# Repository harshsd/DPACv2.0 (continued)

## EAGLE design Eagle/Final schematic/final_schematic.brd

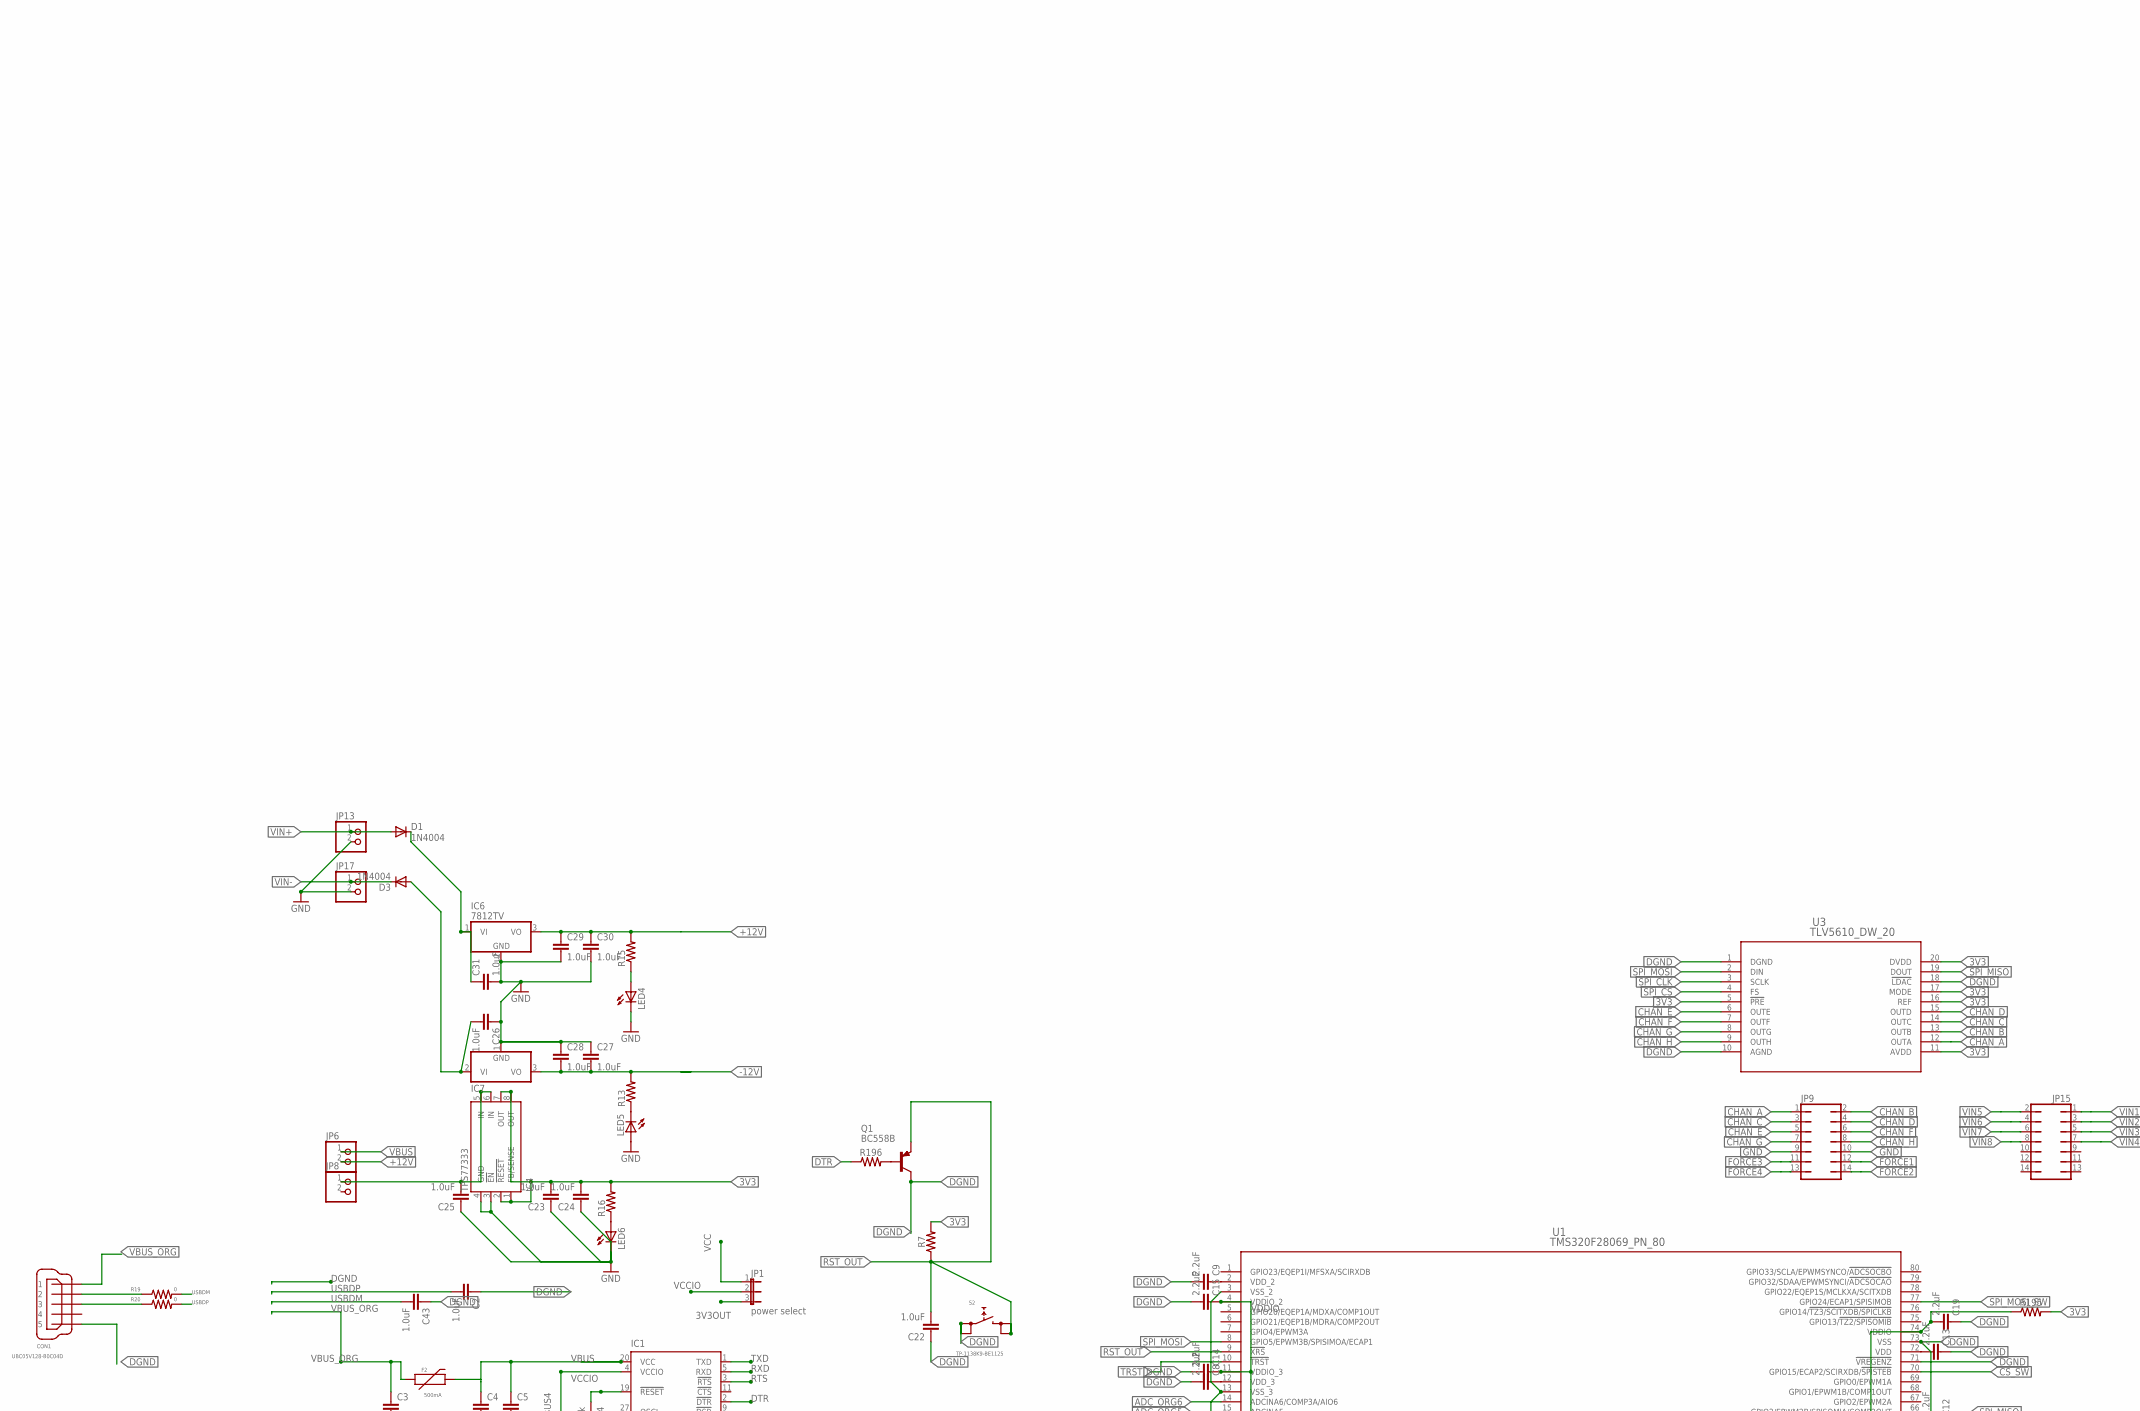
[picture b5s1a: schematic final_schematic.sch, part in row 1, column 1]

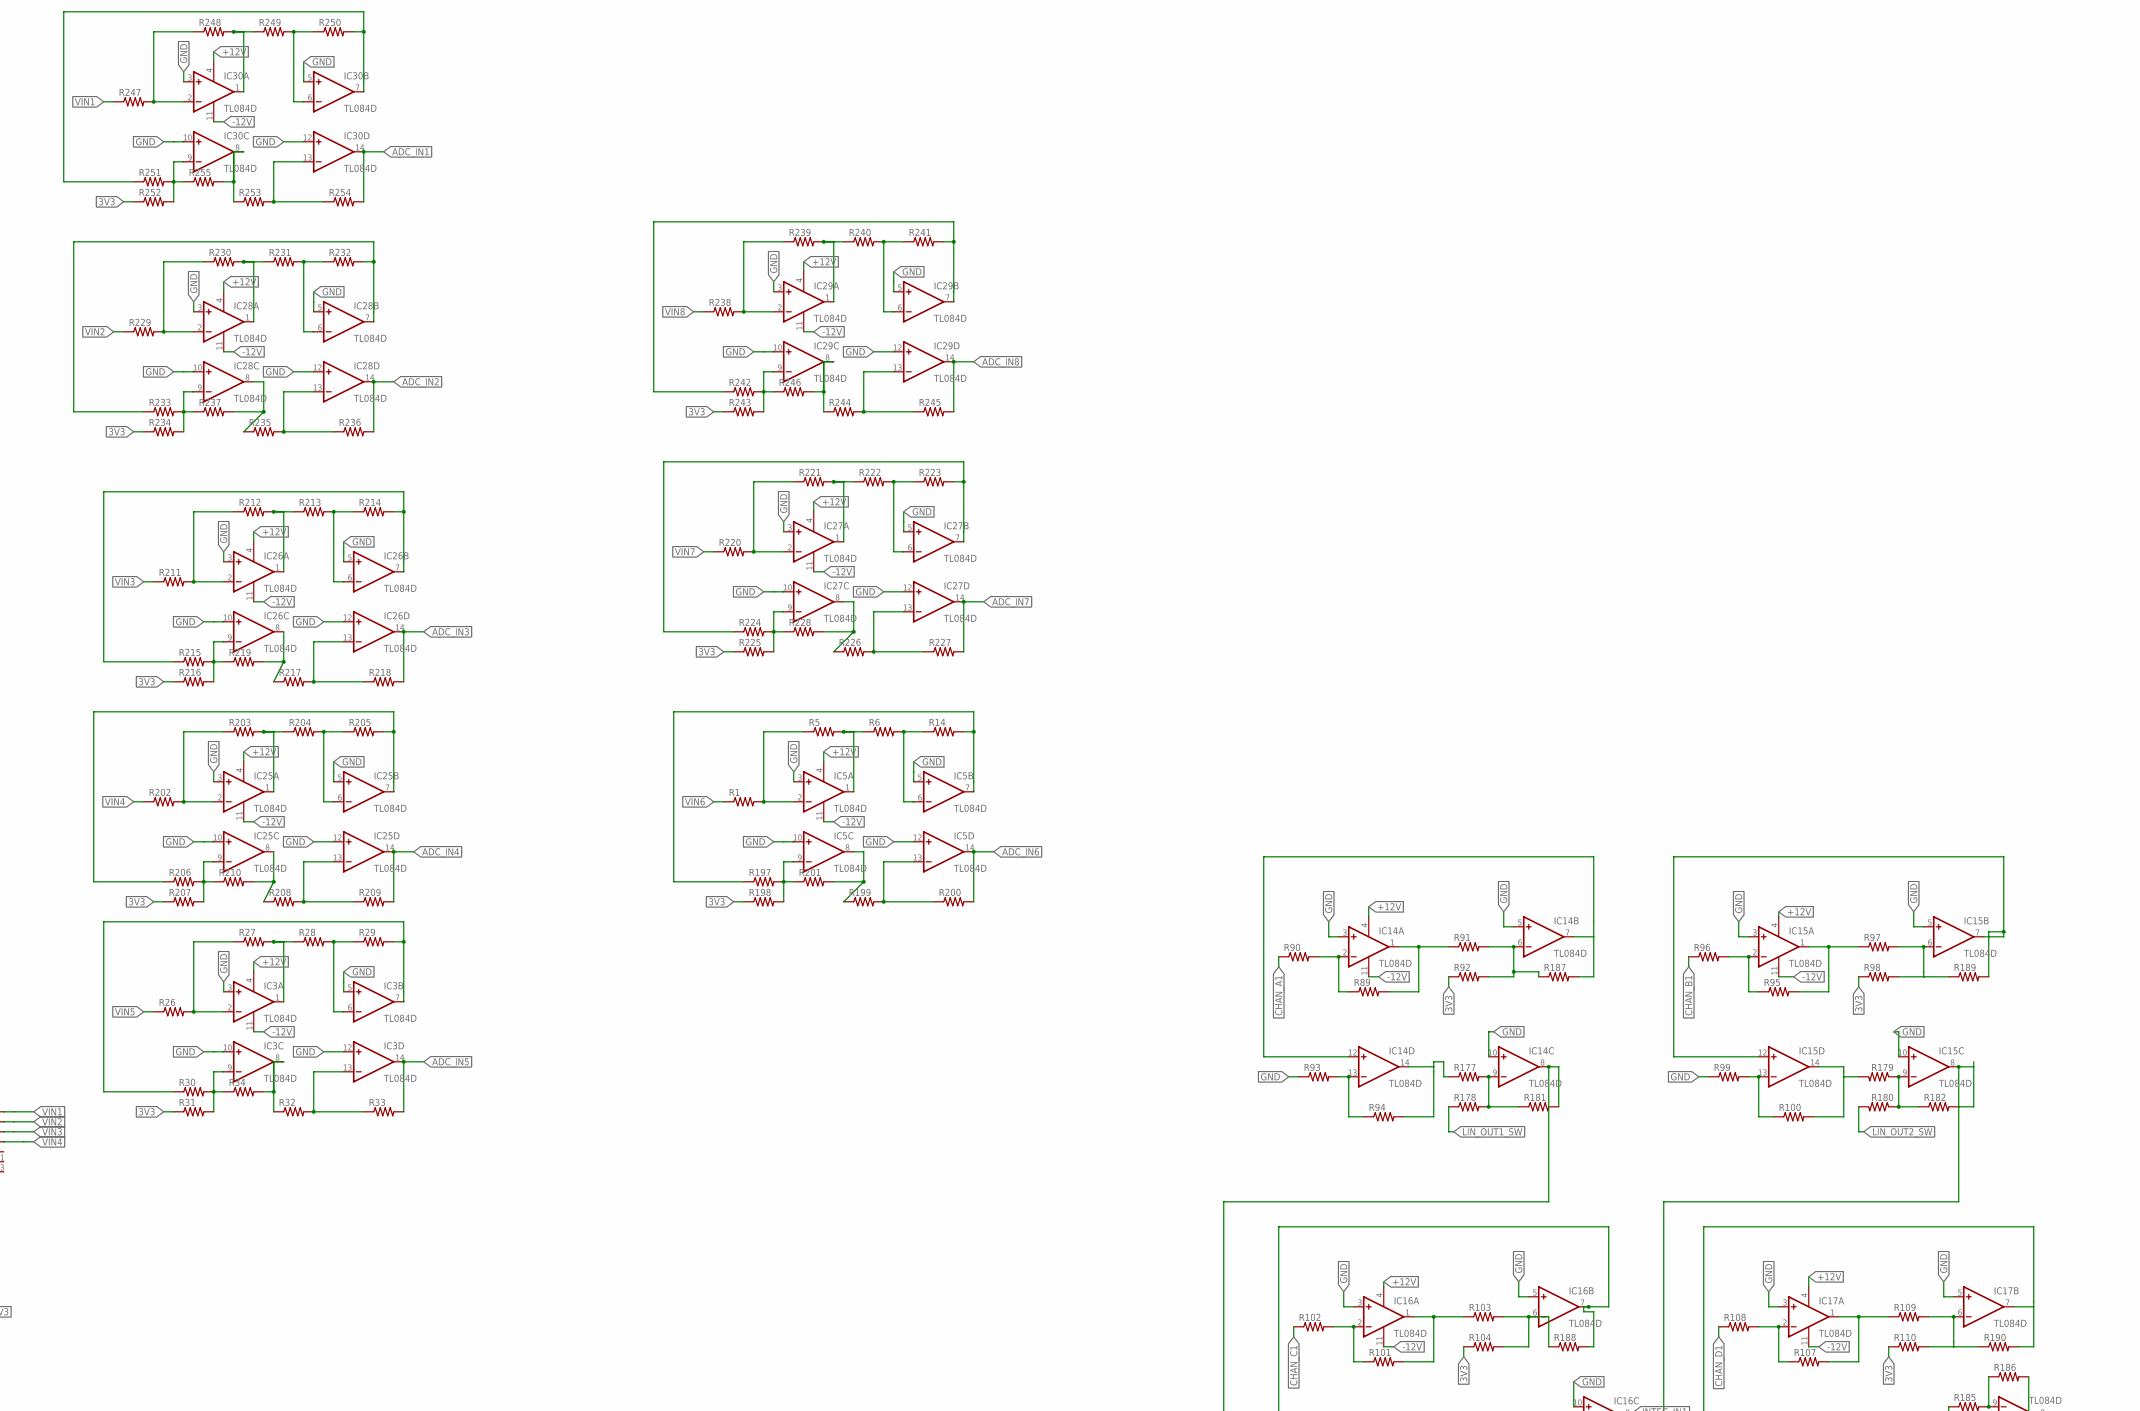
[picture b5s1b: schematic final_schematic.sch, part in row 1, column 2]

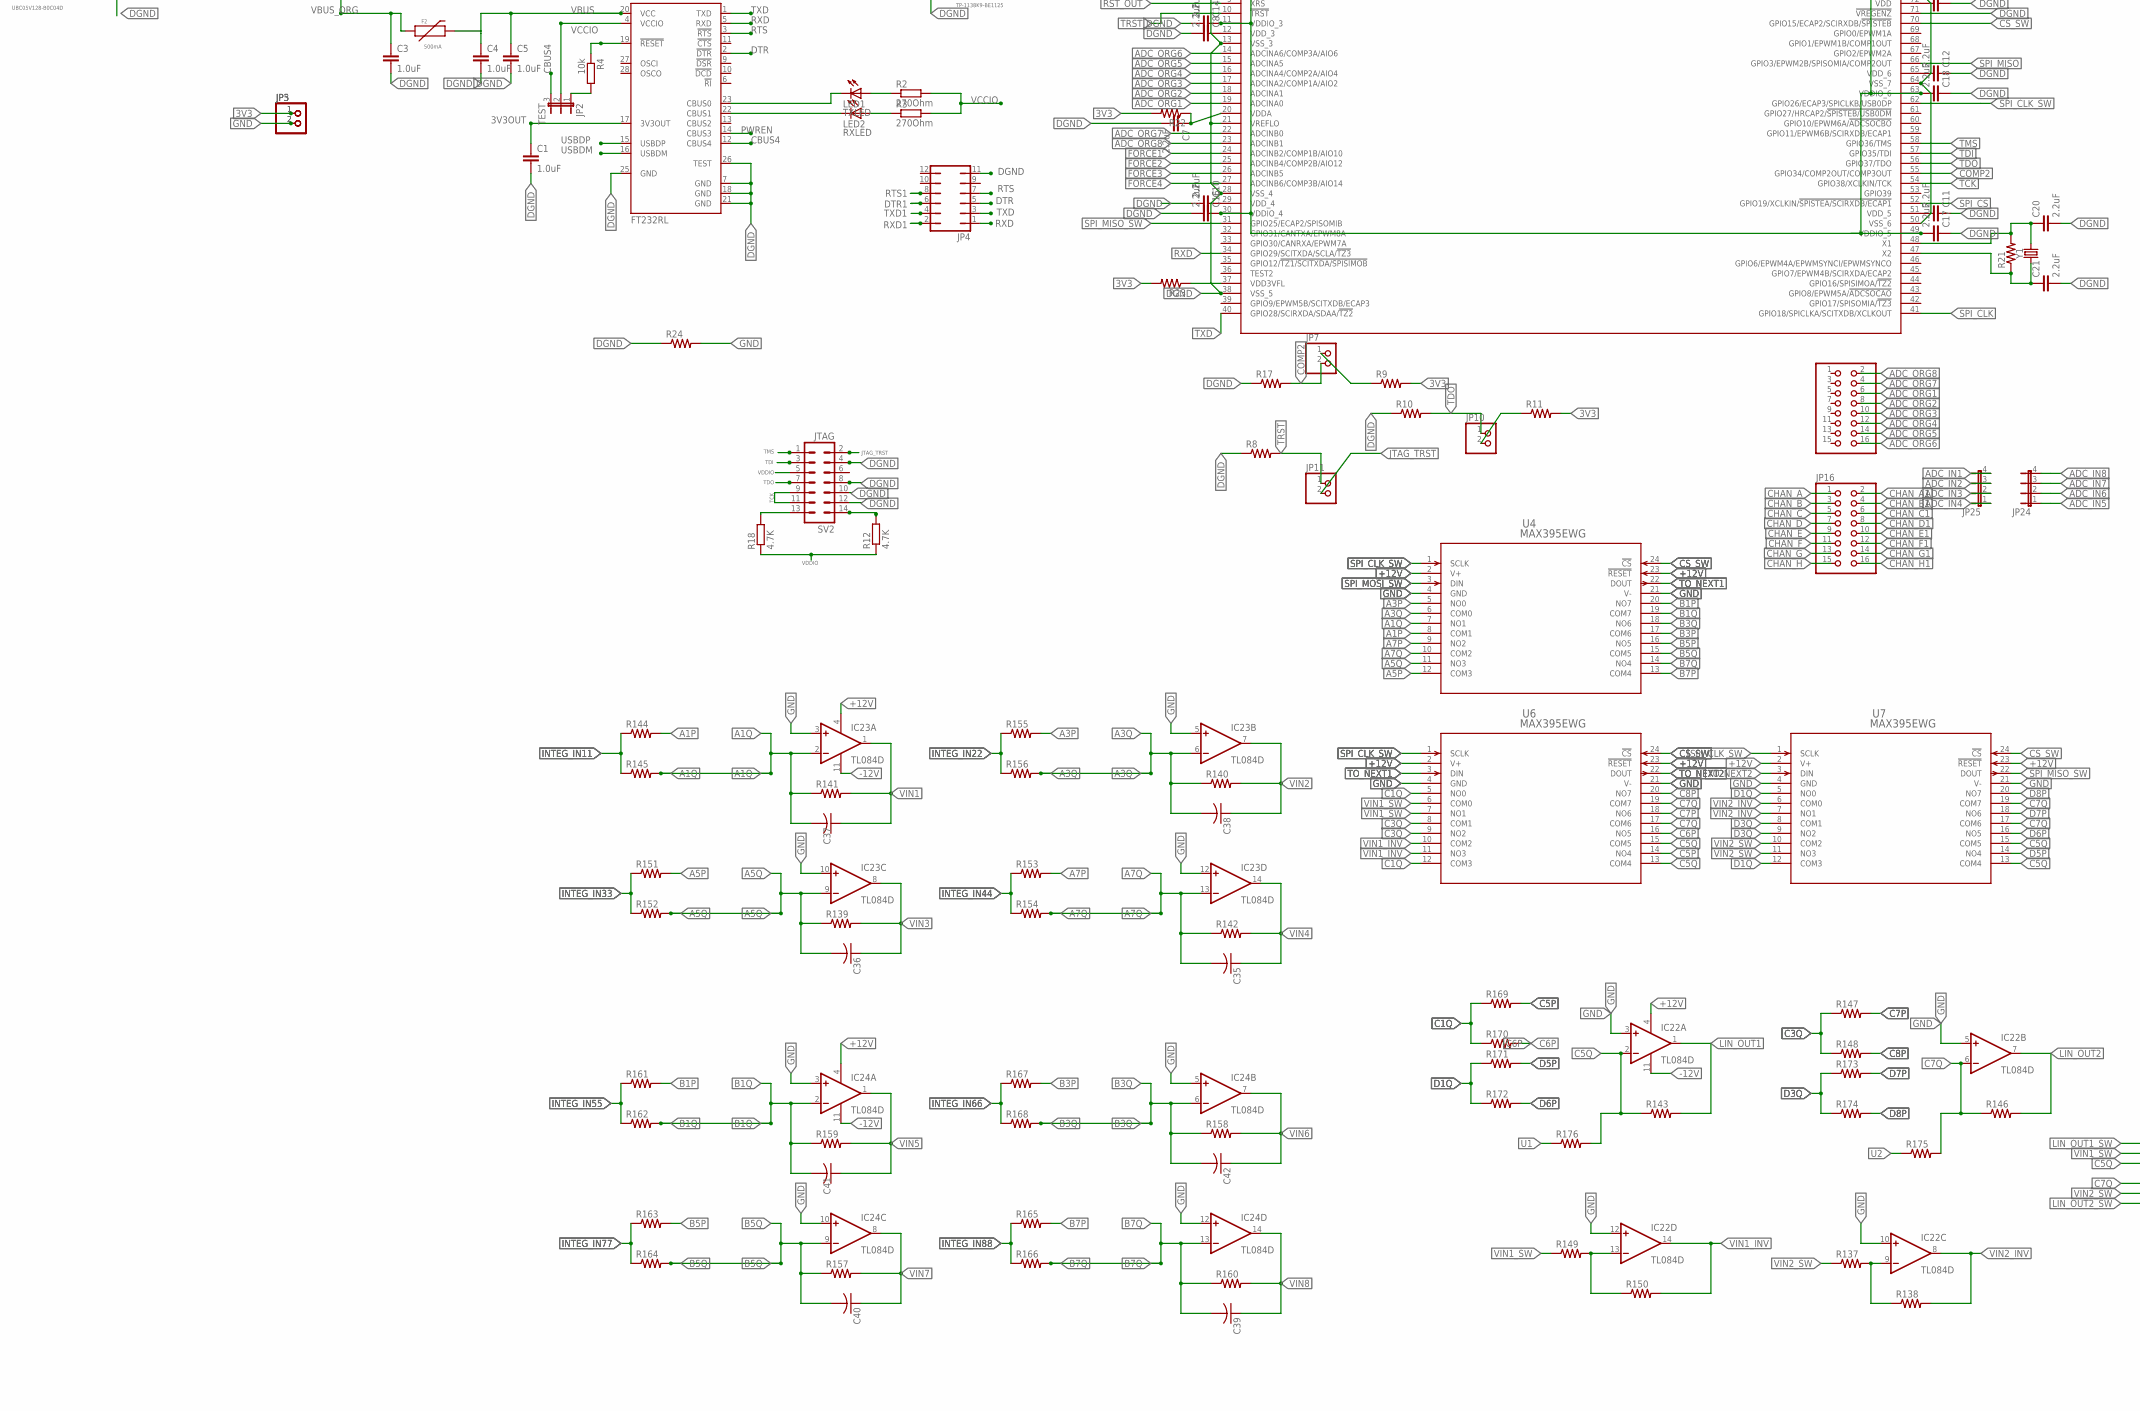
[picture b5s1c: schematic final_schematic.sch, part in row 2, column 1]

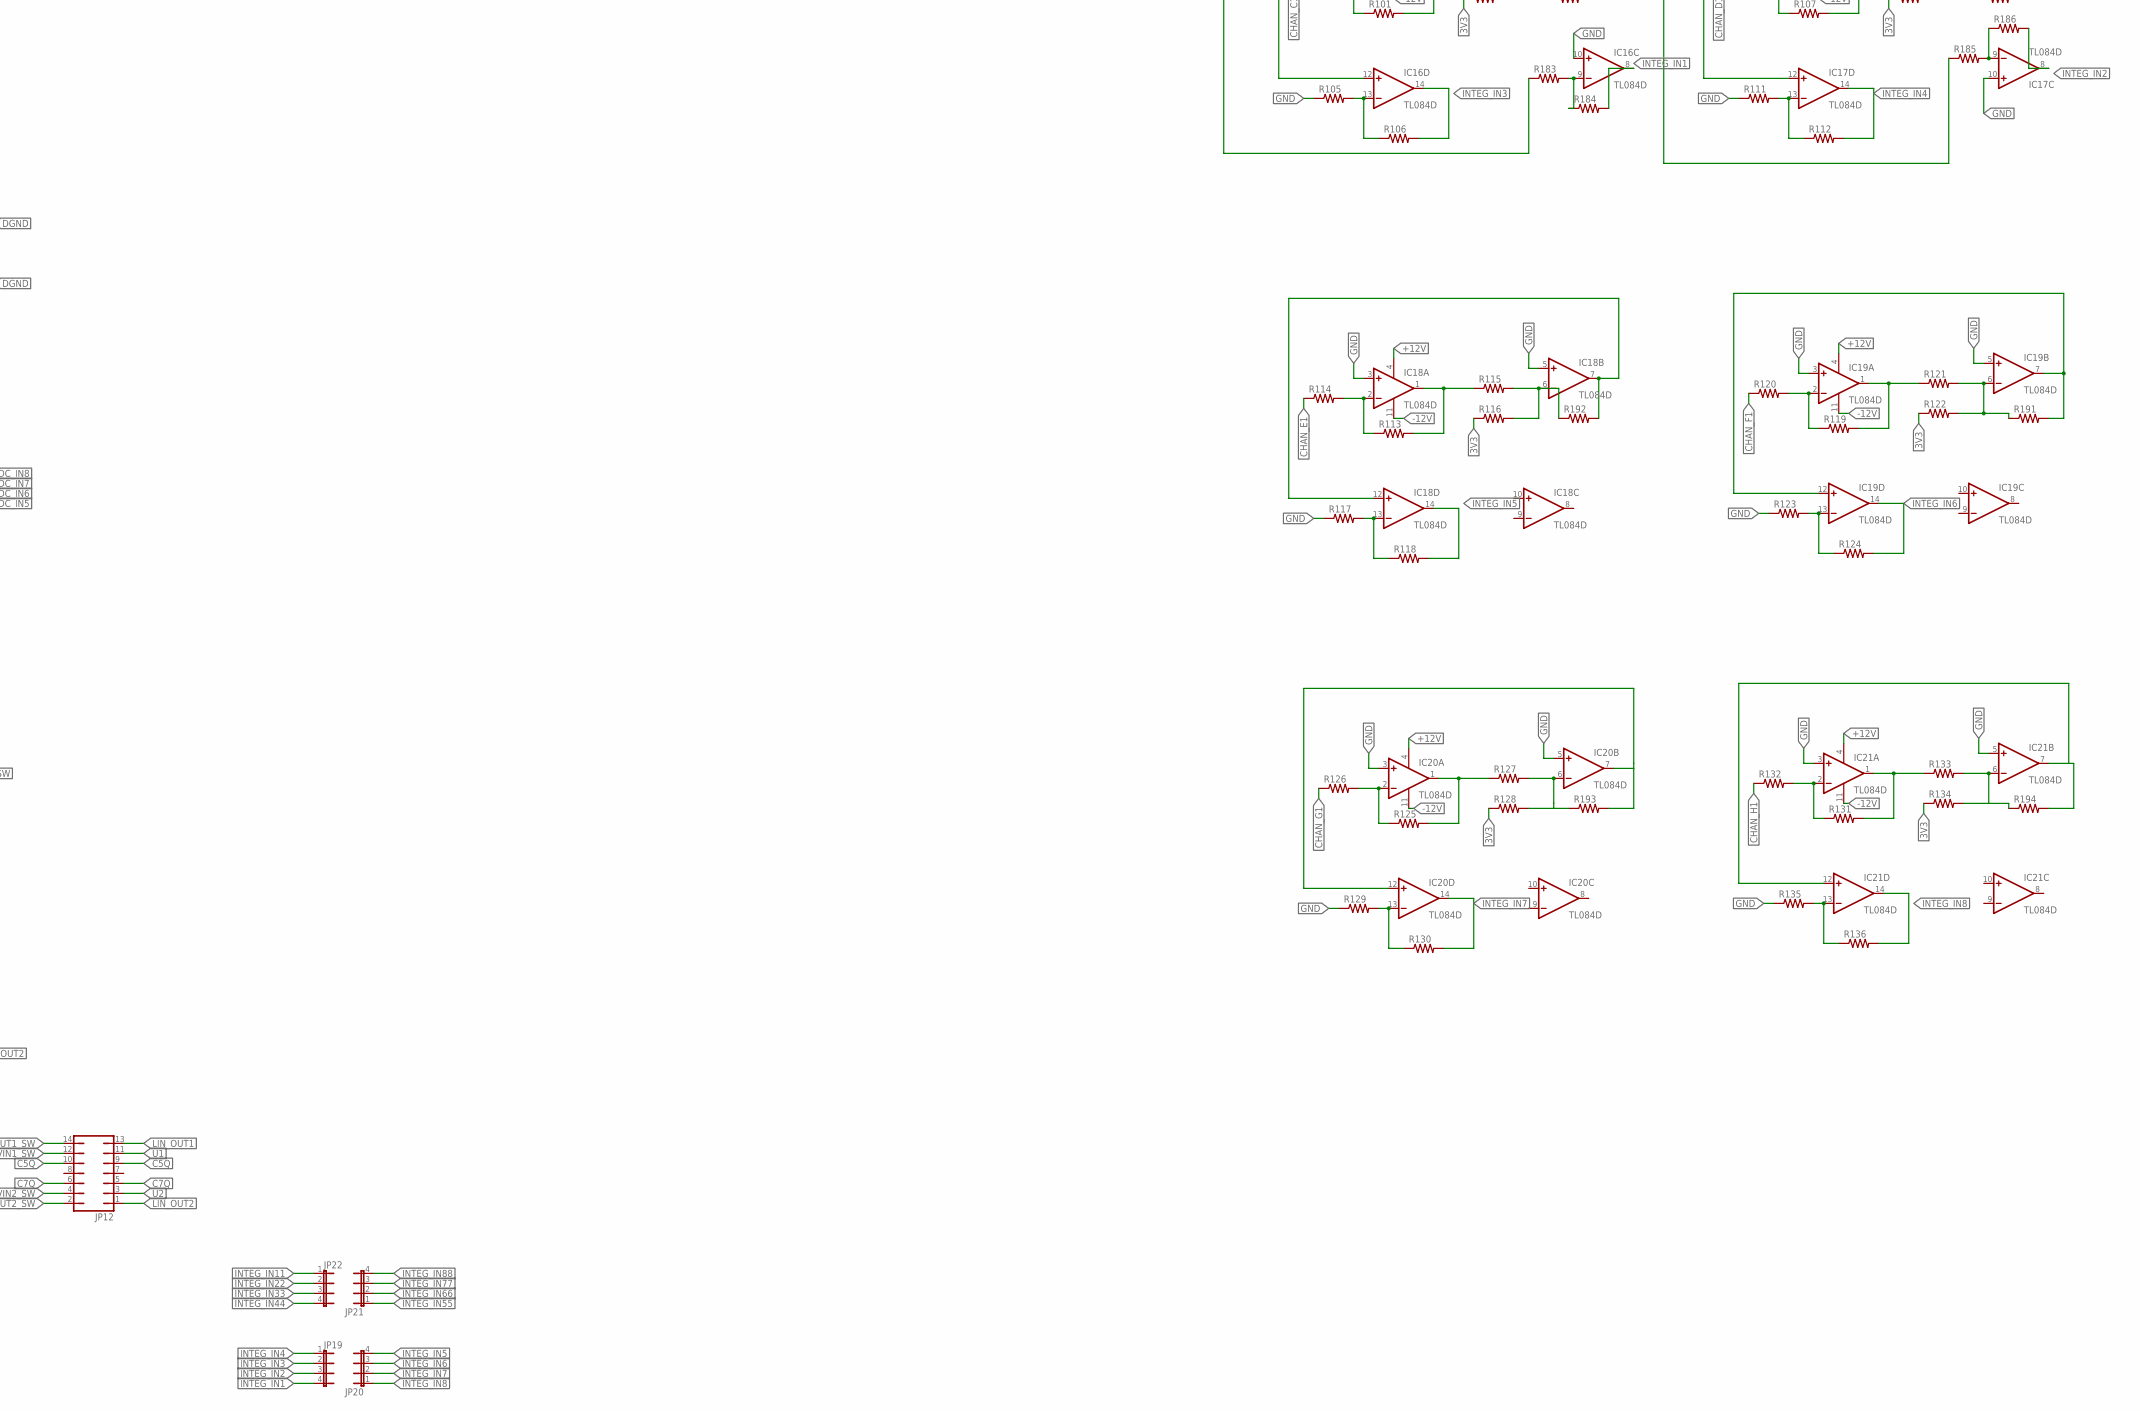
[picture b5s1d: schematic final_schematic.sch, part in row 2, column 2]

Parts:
C1, C2, C3, C4, C5, C22, C23, C24, C25, C26, C27, C28, C29, C30, C31, C43: 1.0uF; 1206
C7, C8, C9, C10, C11, C12, C13, C14, C15, C16, C17, C18, C19, C20, C21: 2.2uF; 1206
C35, C36, C37, C38, C39, C40, C41, C42: C-USC1206; C1206
CON1: UBC05V128-B0C04D; 32005-201
D1, D3: 1N4004; DO41-10
F2: 500mA; PTC-1206
IC1: FT232RL; SSOP28
IC3, IC5, IC14, IC15, IC16, IC17, IC18, IC19, IC20, IC21, IC22, IC23, IC24, IC25, IC26, IC27, IC28, IC29, IC30: TL084D; SO14
IC4: TPS77333; DGK_S-PDSO-G8
IC6: 7812TV; TO220V
IC7: 7912T; TO220H
JP1: power select; JP2
JP2: TEST; JP2
JP3, JP5, JP6, JP7, JP8, JP10, JP11, JP13, JP17: PINHD-1X2; 1X02
JP4: JP6Q
JP9, JP12, JP15: JP7Q
JP16, JP18: PINHD-2X8; 2X08
JP19, JP20, JP21, JP22, JP24, JP25: JP4E; JP4
LED1: TXLED; CHIPLED_1206
LED2: RXLED; CHIPLED_1206
LED4, LED5, LED6: LED3MM
Q1: BC558B; TO92-EBC
R1, R5, R6, R8, R9, R10, R11, R13, R14, R15, R16, R17, R21, R22, R23, R26, R27, R28, R29, R30, R31, R32, R33, R34, R89, R90, R91, R92, R93, R94, R95, R96, R97, R98, R99, R100, R101, R102, R103, R104, R105, R106, R107, R108, R109, R110, R111, R112, R113, R114, R115, R116, R117, R118, R119, R120, R121, R122, R123, R124, R125, R126, R127, R128, R129, R130, R131, R132, R133, R134, R135, R136, R137, R138, R139, R140, R141, R142, R143, R144, R145, R146, R147, R148, R149, R150, R151, R152, R153, R154, R155, R156, R157, R158, R159, R160, R161, R162, R163, R164, R165, R166, R167, R168, R169, R170, R171, R172, R173, R174, R175, R176, R177, R178, R179, R180, R181, R182, R183, R184, R185, R186, R187, R188, R189, R190, R191, R192, R193, R194, R197, R198, R199, R200, R201, R202, R203, R204, R205, R206, R207, R208, R209, R210, R211, R212, R213, R214, R215, R216, R217, R218, R219, R220, R221, R222, R223, R224, R225, R226, R227, R228, R229, R230, R231, R232, R233, R234, R235, R236, R237, R238, R239, R240, R241, R242, R243, R244, R245, R246, R247, R248, R249, R250, R251, R252, R253, R254, R255: R-US_R1206; R1206
R2, R3: 270Ohm; M1206
R4: 10k; M1206
R7, R195, R196: 1206
R12, R18: 4.7K; M1206
R19: 0; R1206
R20: 0; R1206W
R24: R-US_0207/7; 0207/7
S2: TP-1138K9-BE1125; FSMJSMA
SV2: JTAG; MA07-2
U1: TMS320F28069_PN_80; PN80
U3: TLV5610_DW_20; DW20
U4, U6, U7: MAX395EWG; 21-0042B_24
Y1: CRYSTALPTH-HC49UV; HC49U

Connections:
3V3: C23.2, C24.2, IC4.1 (FB/SENSE), IC4.2 (!RESET), IC4.7 (OUT), IC4.8 (OUT), JP3.1, JP5.1, R7.2, R9.2, R11.2, R16.2, R22.2, R23.2, R31.1, R92.1, R98.1, R104.1, R110.1, R116.1, R122.1, R128.1, R134.1, R195.2, R198.1, R207.1, R216.1, R225.1, R234.1, R243.1, R252.1, U3.5 (!PRE), U3.11 (AVDD), U3.16 (REF), U3.17 (MODE), U3.20 (DVDD)
3V3OUT: C1.1, IC1.17 (3V3OUT), JP1.3
+12V: C29.1, C30.1, IC3.4 (V+), IC5.4 (V+), IC6.3 (VO), IC14.4 (V+), IC15.4 (V+), IC16.4 (V+), IC17.4 (V+), IC18.4 (V+), IC19.4 (V+), IC20.4 (V+), IC21.4 (V+), IC22.4 (V+), IC23.4 (V+), IC24.4 (V+), IC25.4 (V+), IC26.4 (V+), IC27.4 (V+), IC28.4 (V+), IC29.4 (V+), IC30.4 (V+), JP6.2, R15.2, U4.2 (V+), U4.23 (!RESET), U6.2 (V+), U6.23 (!RESET), U7.2 (V+), U7.23 (!RESET)
-12V: C27.2, C28.2, IC3.11 (V-), IC5.11 (V-), IC7.3 (VO), IC14.11 (V-), IC15.11 (V-), IC16.11 (V-), IC17.11 (V-), IC18.11 (V-), IC19.11 (V-), IC20.11 (V-), IC21.11 (V-), IC22.11 (V-), IC23.11 (V-), IC24.11 (V-), IC25.11 (V-), IC26.11 (V-), IC27.11 (V-), IC28.11 (V-), IC29.11 (V-), IC30.11 (V-), R13.2
A1P: R144.2, U4.8 (COM1)
A1Q: C37.2, IC23.2 (-IN), R141.1, R145.2, U4.7 (NO1)
A3P: R155.2, U4.5 (NO0)
A3Q: C38.2, IC23.6 (-IN), R140.1, R156.2, U4.6 (COM0)
A5P: R151.2, U4.12 (COM3)
A5Q: C36.2, IC23.9 (-IN), R139.1, R152.2, U4.11 (NO3)
A7P: R153.2, U4.9 (NO2)
A7Q: C35.2, IC23.13 (-IN), R142.1, R154.2, U4.10 (COM2)
ADC_IN1: IC30.14 (OUT), JP25.4, R254.2
ADC_IN2: IC28.14 (OUT), JP25.3, R236.2
ADC_IN3: IC26.14 (OUT), JP25.2, R218.2
ADC_IN4: IC25.14 (OUT), JP25.1, R209.2
ADC_IN5: IC3.14 (OUT), JP24.1, R33.2
ADC_IN6: IC5.14 (OUT), JP24.2, R200.2
ADC_IN7: IC27.14 (OUT), JP24.3, R227.2
ADC_IN8: IC29.14 (OUT), JP24.4, R245.2
ADC_ORG1: JP18.6, U1.19 (ADCINA0)
ADC_ORG2: JP18.8, U1.18 (ADCINA1)
ADC_ORG3: JP18.10, U1.17 (ADCINA2/COMP1A/AIO2)
ADC_ORG4: JP18.12, U1.16 (ADCINA4/COMP2A/AIO4)
ADC_ORG5: JP18.14, U1.15 (ADCINA5)
ADC_ORG6: JP18.16, U1.14 (ADCINA6/COMP3A/AIO6)
ADC_ORG7: JP18.4, U1.22 (ADCINB0)
ADC_ORG8: JP18.2, U1.23 (ADCINB1)
B1P: R161.2, U4.20 (NO7)
B1Q: C41.2, IC24.2 (-IN), R159.1, R162.2, U4.19 (COM7)
B3P: R167.2, U4.17 (COM6)
B3Q: C42.2, IC24.6 (-IN), R158.1, R168.2, U4.18 (NO6)
B5P: R163.2, U4.16 (NO5)
B5Q: C40.2, IC24.9 (-IN), R157.1, R164.2, U4.15 (COM5)
B7P: R165.2, U4.13 (COM4)
B7Q: C39.2, IC24.13 (-IN), R160.1, R166.2, U4.14 (NO4)
C1Q: R169.1, R170.1, U6.5 (NO0), U6.12 (COM3)
C3Q: R147.1, R148.1, U6.8 (COM1), U6.9 (NO2)
C5P: R169.2, U6.14 (NO4)
C5Q: IC22.2 (-IN), JP12.9, JP12.10, R143.1, R176.2, U6.13 (COM4), U6.15 (COM5), U7.13 (COM4), U7.15 (COM5)
C6P: R170.2, U6.16 (NO5)
C7P: R147.2, U6.18 (NO6)
C7Q: IC22.6 (-IN), JP12.5, JP12.6, R146.1, R175.2, U6.17 (COM6), U6.19 (COM7), U7.17 (COM6), U7.19 (COM7)
C8P: R148.2, U6.20 (NO7)
CBUS4: IC1.12 (CBUS4), JP2.3
CHAN_A: JP9.1, JP16.1, U3.12 (OUTA)
CHAN_A1: JP16.2, R90.1
CHAN_B: JP9.2, JP16.3, U3.13 (OUTB)
CHAN_B1: JP16.4, R96.1
CHAN_C: JP9.3, JP16.5, U3.14 (OUTC)
CHAN_C1: JP16.6, R102.1
CHAN_D: JP9.4, JP16.7, U3.15 (OUTD)
CHAN_D1: JP16.8, R108.1
CHAN_E: JP9.5, JP16.9, U3.6 (OUTE)
CHAN_E1: JP16.10, R114.1
CHAN_F: JP9.6, JP16.11, U3.7 (OUTF)
CHAN_F1: JP16.12, R120.1
CHAN_G: JP9.7, JP16.13, U3.8 (OUTG)
CHAN_G1: JP16.14, R126.1
CHAN_H: JP9.8, JP16.15, U3.9 (OUTH)
CHAN_H1: JP16.16, R132.1
COMP2: JP7.2, R17.2, U1.55 (GPIO34/COMP2OUT/COMP3OUT)
CS_SW: U1.70 (GPIO15/ECAP2/SCIRXDB/!SPISTEB), U4.24 (!CS), U6.24 (!CS), U7.24 (!CS)
D1Q: R171.1, R172.1, U7.5 (NO0), U7.12 (COM3)
D3Q: R173.1, R174.1, U7.8 (COM1), U7.9 (NO2)
D5P: R171.2, U7.14 (NO4)
D6P: R172.2, U7.16 (NO5)
D7P: R173.2, U7.18 (NO6)
D8P: R174.2, U7.20 (NO7)
DGND: C1.2, C2.1, C3.2, C4.2, C5.2, C7.2, C8.2, C9.2, C10.2, C11.1, C12.1, C13.1, C14.2, C15.2, C16.2, C17.1, C18.1, C19.1, C20.2, C21.2, C22.1, C43.1, CON1.5, IC1.7 (GND), IC1.18 (GND), IC1.21 (GND), IC1.25 (GND), IC1.26 (TEST), JP4.11, Q1.C, R8.1, R10.1, R17.1, R24.1, S2.P$1 (0), S2.P$2 (0), SV2.4, SV2.8, SV2.10, SV2.12, U1.3 (VSS_2), U1.13 (VSS_3), U1.21 (VREFLO), U1.28 (VSS_4), U1.38 (VSS_5), U1.50 (VSS_6), U1.64 (VSS_7), U1.71 (!VREGENZ), U1.73 (VSS), U3.1 (DGND), U3.10 (AGND), U3.18 (!LDAC)
DTR: IC1.2 (!DTR), JP4.5, R196.1
DTR1: JP4.6
FORCE1: JP9.12, U1.24 (ADCINB2/COMP1B/AIO10)
FORCE2: JP9.14, U1.25 (ADCINB4/COMP2B/AIO12)
FORCE3: JP9.11, U1.26 (ADCINB5)
FORCE4: JP9.13, U1.27 (ADCINB6/COMP3B/AIO14)
GND: C23.1, C24.1, C25.1, C26.1, C27.1, C28.1, C29.2, C30.2, C31.2, IC3.3 (+IN), IC3.5 (+IN), IC3.10 (+IN), IC3.12 (+IN), IC4.3 (!EN), IC4.4 (GND), IC5.3 (+IN), IC5.5 (+IN), IC5.10 (+IN), IC5.12 (+IN), IC6.2 (GND), IC7.1 (GND), IC14.3 (+IN), IC14.5 (+IN), IC14.10 (+IN), IC15.3 (+IN), IC15.5 (+IN), IC15.10 (+IN), IC16.3 (+IN), IC16.5 (+IN), IC16.10 (+IN), IC17.3 (+IN), IC17.5 (+IN), IC17.10 (+IN), IC18.3 (+IN), IC18.5 (+IN), IC19.3 (+IN), IC19.5 (+IN), IC20.3 (+IN), IC20.5 (+IN), IC21.3 (+IN), IC21.5 (+IN), IC22.3 (+IN), IC22.5 (+IN), IC22.10 (+IN), IC22.12 (+IN), IC23.3 (+IN), IC23.5 (+IN), IC23.10 (+IN), IC23.12 (+IN), IC24.3 (+IN), IC24.5 (+IN), IC24.10 (+IN), IC24.12 (+IN), IC25.3 (+IN), IC25.5 (+IN), IC25.10 (+IN), IC25.12 (+IN), IC26.3 (+IN), IC26.5 (+IN), IC26.10 (+IN), IC26.12 (+IN), IC27.3 (+IN), IC27.5 (+IN), IC27.10 (+IN), IC27.12 (+IN), IC28.3 (+IN), IC28.5 (+IN), IC28.10 (+IN), IC28.12 (+IN), IC29.3 (+IN), IC29.5 (+IN), IC29.10 (+IN), IC29.12 (+IN), IC30.3 (+IN), IC30.5 (+IN), IC30.10 (+IN), IC30.12 (+IN), JP3.2, JP5.2, JP9.9, JP9.10, JP13.2, JP17.2, LED4.K (C), LED5.A, LED6.K (C), R24.2, R93.1, R99.1, R105.1, R111.1, R117.1, R123.1, R129.1, R135.1, U4.4 (GND), U4.21 (V-), U6.4 (GND), U6.21 (V-), U7.4 (GND), U7.21 (V-)
INTEG_IN1: IC16.8 (OUT), JP19.4, R184.2
INTEG_IN2: IC17.8 (OUT), JP19.3, R186.2
INTEG_IN3: IC16.14 (OUT), JP19.2, R106.2
INTEG_IN4: IC17.14 (OUT), JP19.1, R112.2
INTEG_IN5: IC18.14 (OUT), JP20.4, R118.2
INTEG_IN6: IC19.14 (OUT), JP20.3, R124.2
INTEG_IN7: IC20.14 (OUT), JP20.2, R130.2
INTEG_IN8: IC21.14 (OUT), JP20.1, R136.2
INTEG_IN11: JP22.1, R144.1, R145.1
INTEG_IN22: JP22.2, R155.1, R156.1
INTEG_IN33: JP22.3, R151.1, R152.1
INTEG_IN44: JP22.4, R153.1, R154.1
INTEG_IN55: JP21.1, R161.1, R162.1
INTEG_IN66: JP21.2, R167.1, R168.1
INTEG_IN77: JP21.3, R163.1, R164.1
INTEG_IN88: JP21.4, R165.1, R166.1
JTAG_TRST: JP11.2, SV2.2
LIN_OUT1: IC22.1 (OUT), JP12.13, R143.2
LIN_OUT1_SW: JP12.14, R178.1
LIN_OUT2: IC22.7 (OUT), JP12.1, R146.2
LIN_OUT2_SW: JP12.2, R180.2
unnamed: C7.1, R22.1, U1.20 (VDDA)
unnamed: C8.1, U1.12 (VDD_3)
unnamed: C9.1, U1.2 (VDD_2)
unnamed: LED1.A, R2.1
unnamed: C10.1, U1.29 (VDD_4)
unnamed: C11.2, U1.51 (VDD_5)
unnamed: C12.2, U1.65 (VDD_6)
unnamed: C13.2, U1.72 (VDD)
unnamed: LED2.A, R3.1
unnamed: IC1.23 (CBUS0), LED1.C
unnamed: IC1.22 (CBUS1), LED2.C
unnamed: CON1.2, R19.1
unnamed: CON1.3, R20.1
unnamed: JP2.1, R4.2
unnamed: C20.1, R21.2, U1.48 (X1), Y1.2
unnamed: R23.1, U1.37 (VDD3VFL)
unnamed: C21.1, R21.1, U1.47 (X2), Y1.1
unnamed: JP7.1, R9.1
unnamed: Q1.B, R196.2
unnamed: JP10.2, R11.1
unnamed: R18.2, SV2.13
unnamed: C26.2, D3.A, IC7.2 (VI)
unnamed: R12.2, SV2.14
unnamed: C25.2, IC4.5 (IN), IC4.6 (IN), JP8.1
unnamed: LED4.A, R15.1
unnamed: C31.1, D1.C, IC6.1 (VI)
unnamed: IC14.2 (-IN), R89.1, R90.2
unnamed: LED5.K (C), R13.1
unnamed: LED6.A, R16.1
unnamed: IC3.2 (-IN), R26.2, R27.1
unnamed: IC3.1 (OUT), R27.2, R28.1
unnamed: IC3.6 (-IN), R28.2, R29.1
unnamed: IC5.2 (-IN), R1.2, R5.1
unnamed: IC3.8 (OUT), R32.1, R34.2
unnamed: IC14.1 (OUT), R89.2, R91.1
unnamed: IC3.13 (-IN), R32.2, R33.1
unnamed: IC3.9 (-IN), R30.2, R31.2, R34.1
unnamed: IC14.6 (-IN), R91.2, R92.2, R187.1
unnamed: IC14.13 (-IN), R93.2, R94.1
unnamed: IC14.8 (OUT), R181.2, R183.1
unnamed: IC14.7 (OUT), IC14.12 (+IN), R187.2
unnamed: IC15.2 (-IN), R95.1, R96.2
unnamed: IC15.1 (OUT), R95.2, R97.1
unnamed: IC15.6 (-IN), R97.2, R98.2, R189.1
unnamed: IC15.13 (-IN), R99.2, R100.1
unnamed: IC15.14 (OUT), R100.2, R179.2
unnamed: IC15.7 (OUT), IC15.12 (+IN), R189.2
unnamed: IC16.2 (-IN), R101.1, R102.2
unnamed: IC16.1 (OUT), R101.2, R103.1
unnamed: IC16.6 (-IN), R103.2, R104.2, R188.1
unnamed: IC16.13 (-IN), R105.2, R106.1
unnamed: IC14.9 (-IN), R177.2, R178.2, R181.1
unnamed: IC16.7 (OUT), IC16.12 (+IN), R188.2
unnamed: IC17.2 (-IN), R107.1, R108.2
unnamed: IC17.1 (OUT), R107.2, R109.1
unnamed: IC17.6 (-IN), R109.2, R110.2, R190.1
unnamed: IC17.13 (-IN), R111.2, R112.1
unnamed: IC15.9 (-IN), R179.1, R180.1, R182.1
unnamed: IC17.7 (OUT), IC17.12 (+IN), R190.2
unnamed: IC18.2 (-IN), R113.1, R114.2
unnamed: IC18.1 (OUT), R113.2, R115.1
unnamed: IC18.6 (-IN), R115.2, R116.2, R192.1
unnamed: IC18.13 (-IN), R117.2, R118.1
unnamed: IC14.14 (OUT), R94.2, R177.1
unnamed: IC18.7 (OUT), IC18.12 (+IN), R192.2
unnamed: IC19.2 (-IN), R119.1, R120.2
unnamed: IC19.1 (OUT), R119.2, R121.1
unnamed: IC19.6 (-IN), R121.2, R122.2, R191.1
unnamed: IC19.13 (-IN), R123.2, R124.1
unnamed: IC15.8 (OUT), R182.2, R185.1
unnamed: IC19.7 (OUT), IC19.12 (+IN), R191.2
unnamed: IC20.2 (-IN), R125.1, R126.2
unnamed: IC20.1 (OUT), R125.2, R127.1
unnamed: IC20.6 (-IN), R127.2, R128.2, R193.1
unnamed: IC20.13 (-IN), R129.2, R130.1
unnamed: IC17.9 (-IN), R185.2, R186.1
unnamed: IC20.7 (OUT), IC20.12 (+IN), R193.2
unnamed: IC21.2 (-IN), R131.1, R132.2
unnamed: IC21.1 (OUT), R131.2, R133.1
unnamed: IC21.6 (-IN), R133.2, R134.2, R194.1
unnamed: IC21.13 (-IN), R135.2, R136.1
unnamed: IC16.9 (-IN), R183.2, R184.1
unnamed: IC21.7 (OUT), IC21.12 (+IN), R194.2
unnamed: IC22.13 (-IN), R149.2, R150.1
unnamed: IC22.9 (-IN), R137.2, R138.1
unnamed: IC5.1 (OUT), R5.2, R6.1
unnamed: IC3.7 (OUT), R29.2, R30.1
unnamed: IC5.6 (-IN), R6.2, R14.1
unnamed: IC5.8 (OUT), R199.1, R201.2
unnamed: IC5.13 (-IN), R199.2, R200.1
unnamed: IC5.9 (-IN), R197.2, R198.2, R201.1
unnamed: IC5.7 (OUT), R14.2, R197.1
unnamed: IC25.2 (-IN), R202.2, R203.1
unnamed: IC25.1 (OUT), R203.2, R204.1
unnamed: IC25.6 (-IN), R204.2, R205.1
unnamed: IC25.8 (OUT), R208.1, R210.2
unnamed: IC25.13 (-IN), R208.2, R209.1
unnamed: IC25.9 (-IN), R206.2, R207.2, R210.1
unnamed: IC25.7 (OUT), R205.2, R206.1
unnamed: IC26.2 (-IN), R211.2, R212.1
unnamed: IC26.1 (OUT), R212.2, R213.1
unnamed: IC26.6 (-IN), R213.2, R214.1
unnamed: IC26.8 (OUT), R217.1, R219.2
unnamed: IC26.13 (-IN), R217.2, R218.1
unnamed: IC26.9 (-IN), R215.2, R216.2, R219.1
unnamed: IC26.7 (OUT), R214.2, R215.1
unnamed: IC27.2 (-IN), R220.2, R221.1
unnamed: IC27.1 (OUT), R221.2, R222.1
unnamed: IC27.6 (-IN), R222.2, R223.1
unnamed: IC27.8 (OUT), R226.1, R228.2
unnamed: IC27.13 (-IN), R226.2, R227.1
unnamed: IC27.9 (-IN), R224.2, R225.2, R228.1
unnamed: IC27.7 (OUT), R223.2, R224.1
unnamed: IC28.2 (-IN), R229.2, R230.1
unnamed: IC28.1 (OUT), R230.2, R231.1
unnamed: IC28.6 (-IN), R231.2, R232.1
unnamed: IC28.8 (OUT), R235.1, R237.2
unnamed: IC28.13 (-IN), R235.2, R236.1
unnamed: IC28.9 (-IN), R233.2, R234.2, R237.1
unnamed: IC28.7 (OUT), R232.2, R233.1
unnamed: IC29.2 (-IN), R238.2, R239.1
unnamed: IC29.1 (OUT), R239.2, R240.1
unnamed: IC29.6 (-IN), R240.2, R241.1
unnamed: IC29.8 (OUT), R244.1, R246.2
unnamed: IC29.13 (-IN), R244.2, R245.1
unnamed: IC29.9 (-IN), R242.2, R243.2, R246.1
unnamed: IC29.7 (OUT), R241.2, R242.1
unnamed: IC30.2 (-IN), R247.2, R248.1
unnamed: IC30.1 (OUT), R248.2, R249.1
unnamed: IC30.6 (-IN), R249.2, R250.1
unnamed: IC30.8 (OUT), R253.1, R255.2
unnamed: IC30.13 (-IN), R253.2, R254.1
unnamed: IC30.9 (-IN), R251.2, R252.2, R255.1
unnamed: IC30.7 (OUT), R250.2, R251.1
PWREN: IC1.14 (CBUS3)
RESET: IC1.19 (!RESET), R4.1
RST_OUT: C22.2, Q1.E, R7.1, S2.P$3 (1), S2.P$4 (1), U1.9 (!XRS)
RTS: IC1.3 (!RTS), JP4.7
RTS1: JP4.8
RXD: IC1.5 (RXD), JP4.1, U1.34 (GPIO29/SCITXDA/SCLA/!TZ3)
RXD1: JP4.2
SPI_CLK: U1.41 (GPIO18/SPICLKA/SCITXDB/XCLKOUT), U3.3 (SCLK)
SPI_CLK_SW: U1.62 (GPIO26/ECAP3/SPICLKB/USB0DP), U4.1 (SCLK), U6.1 (SCLK), U7.1 (SCLK)
SPI_CS: U1.52 (GPIO19/XCLKIN/!SPISTEA/SCIRXDB/ECAP1), U3.4 (FS)
SPI_MISO: U1.66 (GPIO3/EPWM2B/SPISOMIA/COMP2OUT), U3.19 (DOUT)
SPI_MISO_SW: U1.31 (GPIO25/ECAP2/SPISOMIB), U7.22 (DOUT)
SPI_MOSI: U1.8 (GPIO5/EPWM3B/SPISIMOA/ECAP1), U3.2 (DIN)
SPI_MOSI_SW: U1.77 (GPIO24/ECAP1/SPISIMOB), U4.3 (DIN)
TCK: SV2.9, SV2.11, U1.54 (GPIO38/XCLKIN/TCK)
TDI: SV2.3, U1.57 (GPIO35/TDI)
TDO: JP10.1, R10.2, SV2.7, U1.56 (GPIO37/TDO)
TMS: SV2.1, U1.58 (GPIO36/TMS)
TO_NEXT1: U4.22 (DOUT), U6.3 (DIN)
TO_NEXT2: U6.22 (DOUT), U7.3 (DIN)
TRST: JP11.1, R8.2, U1.10 (!TRST)
TXD: IC1.1 (TXD), JP4.3, U1.40 (GPIO28/SCIRXDA/SDAA/!TZ2)
TXD1: JP4.4
U1: JP12.11, R176.1
U2: JP12.3, R175.1
USBDM: C43.2, IC1.16 (USBDM), R19.2
USBDP: C2.2, IC1.15 (USBDP), R20.2
VBUS: C4.1, C5.1, F2.2, IC1.20 (VCC), JP6.1
VBUS_ORG: C3.1, CON1.1, F2.1
VCC: JP1.1
VCCIO: IC1.4 (VCCIO), JP1.2, JP2.2, R2.2, R3.2
VDDIO: C14.1, C15.1, C16.1, C17.2, C18.2, C19.2, R12.1, R18.1, R195.1, SV2.5, U1.4 (VDDIO_2), U1.11 (VDDIO_3), U1.30 (VDDIO_4), U1.49 (VDDIO_5), U1.63 (VDDIO_6), U1.74 (VDDIO)
VIN1: C37.1, IC23.1 (OUT), JP15.1, R141.2, R247.1
VIN1_INV: IC22.14 (OUT), R150.2, U6.10 (COM2), U6.11 (NO3)
VIN1_SW: JP12.12, R149.1, U6.6 (COM0), U6.7 (NO1)
VIN2: C38.1, IC23.7 (OUT), JP15.3, R140.2, R229.1
VIN2_INV: IC22.8 (OUT), R138.2, U7.6 (COM0), U7.7 (NO1)
VIN2_SW: JP12.4, R137.1, U7.10 (COM2), U7.11 (NO3)
VIN3: C36.1, IC23.8 (OUT), JP15.5, R139.2, R211.1
VIN4: C35.1, IC23.14 (OUT), JP15.7, R142.2, R202.1
VIN5: C41.1, IC24.1 (OUT), JP15.2, R26.1, R159.2
VIN6: C42.1, IC24.7 (OUT), JP15.4, R1.1, R158.2
VIN7: C40.1, IC24.8 (OUT), JP15.6, R157.2, R220.1
VIN8: C39.1, IC24.14 (OUT), JP15.8, R160.2, R238.1
VIN+: D1.A, JP13.1
VIN-: D3.C, JP17.1
